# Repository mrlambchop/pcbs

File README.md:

pcbs
====

Various PCBs I fabbed at OSH Park

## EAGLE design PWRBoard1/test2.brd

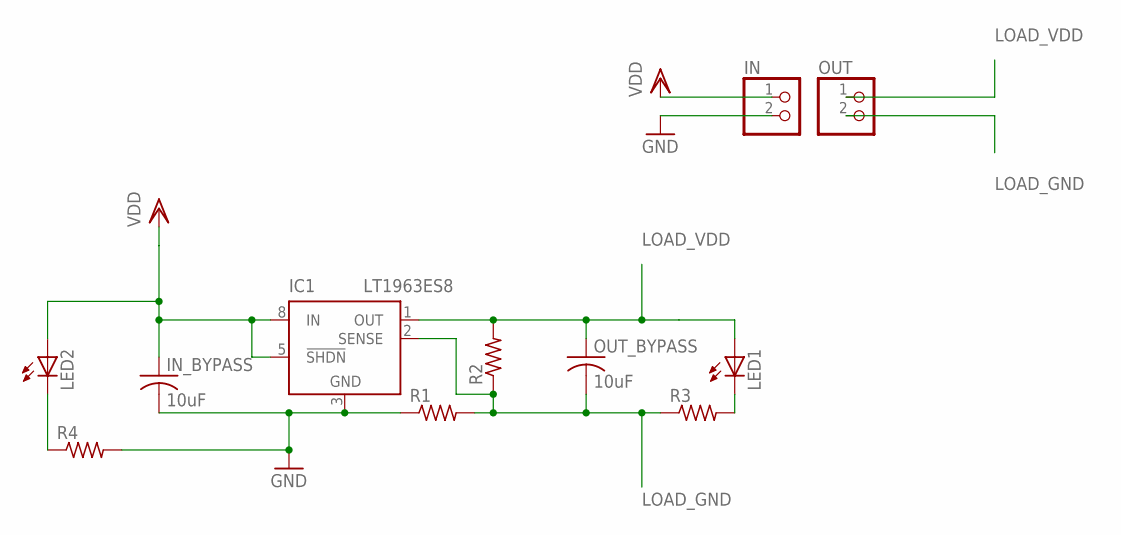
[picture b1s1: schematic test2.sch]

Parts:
IC1: LT1963ES8; SOIC8
IN: PINHD-1X2; 1X02
IN_BYPASS: 10uF; C1206
LED1, LED2: LEDCHIPLED_1206; CHIPLED_1206
OUT: PINHD-1X2; 1X02
OUT_BYPASS: 10uF; C1206
R1, R2, R3, R4: R-US_R1206; R1206

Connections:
GND: IC1.3 (GND), IC1.6 (GND), IC1.7 (GND), IN.2, IN_BYPASS.2, R1.1, R4.2
LOAD_GND: IC1.2 (SENSE), OUT.2, OUT_BYPASS.2, R1.2, R2.1, R3.1
LOAD_VDD: IC1.1 (OUT), LED1.A, OUT.1, OUT_BYPASS.1, R2.2
unnamed: LED2.C, R4.1
unnamed: LED1.C, R3.2
VDD: IC1.5 (!SHDN), IC1.8 (IN), IN.1, IN_BYPASS.1, LED2.A

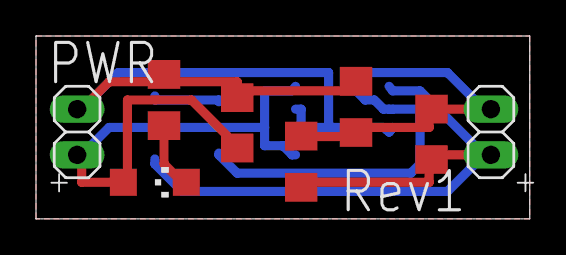
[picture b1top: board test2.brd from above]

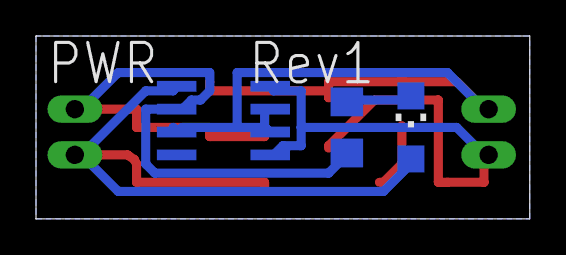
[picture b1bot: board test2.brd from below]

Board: 2 copper layers, 27.4 x 10.2 mm, 11 parts (3 on the bottom side), 6 nets.

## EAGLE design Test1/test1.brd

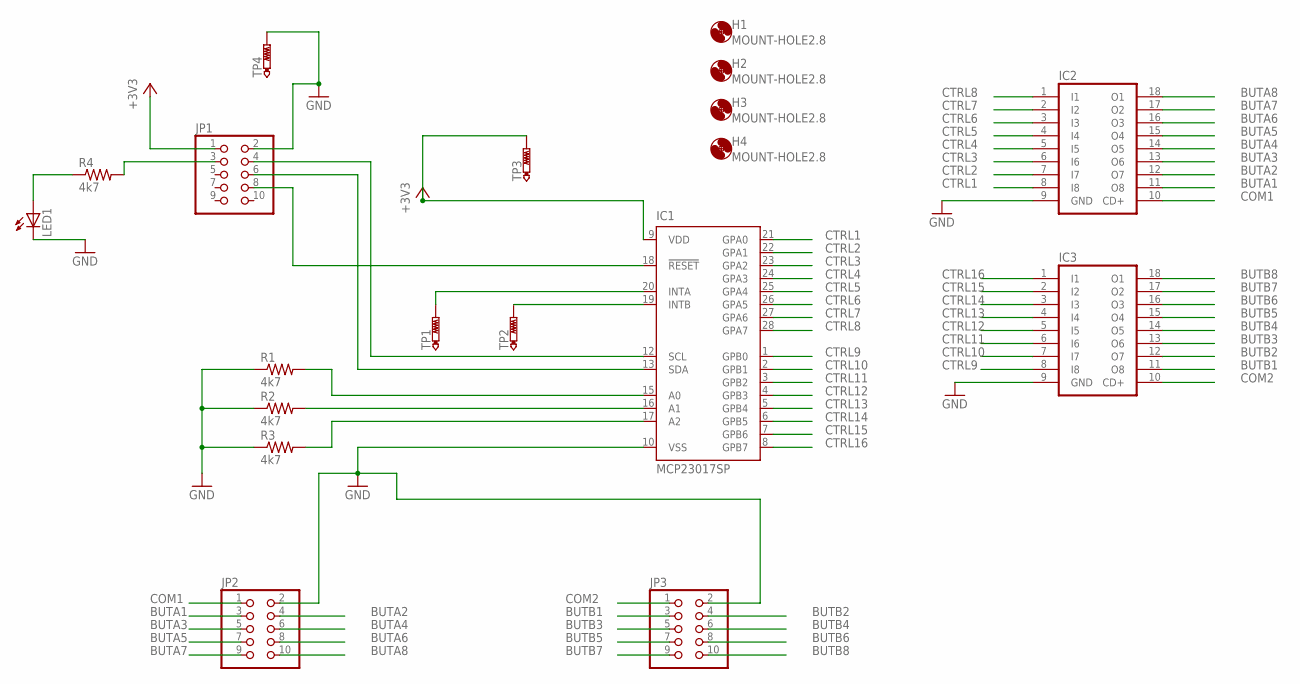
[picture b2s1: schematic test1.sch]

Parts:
H1, H2, H3, H4: MOUNT-HOLE2.8; 2,8
IC1: MCP23017SP; DIL28-3
IC2, IC3: ULN2803A; DIL18
JP1, JP2, JP3: PINHD-2X5; 2X05
LED1: LED5MM
R1, R2, R3, R4: 4k7; 0207/2V
TP1, TP2, TP3, TP4: PTR1B2,54; B2,54

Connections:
+3V3: IC1.9 (VDD), JP1.1, TP3.TP
BUTA1: IC2.11 (O8), JP2.3
BUTA2: IC2.12 (O7), JP2.4
BUTA3: IC2.13 (O6), JP2.5
BUTA4: IC2.14 (O5), JP2.6
BUTA5: IC2.15 (O4), JP2.7
BUTA6: IC2.16 (O3), JP2.8
BUTA7: IC2.17 (O2), JP2.9
BUTA8: IC2.18 (O1), JP2.10
BUTB1: IC3.11 (O8), JP3.3
BUTB2: IC3.12 (O7), JP3.4
BUTB3: IC3.13 (O6), JP3.5
BUTB4: IC3.14 (O5), JP3.6
BUTB5: IC3.15 (O4), JP3.7
BUTB6: IC3.16 (O3), JP3.8
BUTB7: IC3.17 (O2), JP3.9
BUTB8: IC3.18 (O1), JP3.10
COM1: IC2.10 (CD+), JP2.1
COM2: IC3.10 (CD+), JP3.1
CTRL1: IC1.21 (GPA0), IC2.8 (I8)
CTRL2: IC1.22 (GPA1), IC2.7 (I7)
CTRL3: IC1.23 (GPA2), IC2.6 (I6)
CTRL4: IC1.24 (GPA3), IC2.5 (I5)
CTRL5: IC1.25 (GPA4), IC2.4 (I4)
CTRL6: IC1.26 (GPA5), IC2.3 (I3)
CTRL7: IC1.27 (GPA6), IC2.2 (I2)
CTRL8: IC1.28 (GPA7), IC2.1 (I1)
CTRL9: IC1.1 (GPB0), IC3.8 (I8)
CTRL10: IC1.2 (GPB1), IC3.7 (I7)
CTRL11: IC1.3 (GPB2), IC3.6 (I6)
CTRL12: IC1.4 (GPB3), IC3.5 (I5)
CTRL13: IC1.5 (GPB4), IC3.4 (I4)
CTRL14: IC1.6 (GPB5), IC3.3 (I3)
CTRL15: IC1.7 (GPB6), IC3.2 (I2)
CTRL16: IC1.8 (GPB7), IC3.1 (I1)
GND: IC1.10 (VSS), IC2.9 (GND), IC3.9 (GND), JP1.2, JP2.2, JP3.2, LED1.K (C), R1.1, R2.1, R3.1, TP4.TP
unnamed: IC1.13 (SDA), JP1.6
unnamed: IC1.12 (SCL), JP1.4
unnamed: IC1.15 (A0), R1.2
unnamed: IC1.16 (A1), R2.2
unnamed: IC1.17 (A2), R3.2
unnamed: IC1.18 (!RESET), JP1.8
unnamed: JP1.3, R4.2
unnamed: LED1.A, R4.1
unnamed: IC1.20 (INTA), TP1.TP
unnamed: IC1.19 (INTB), TP2.TP

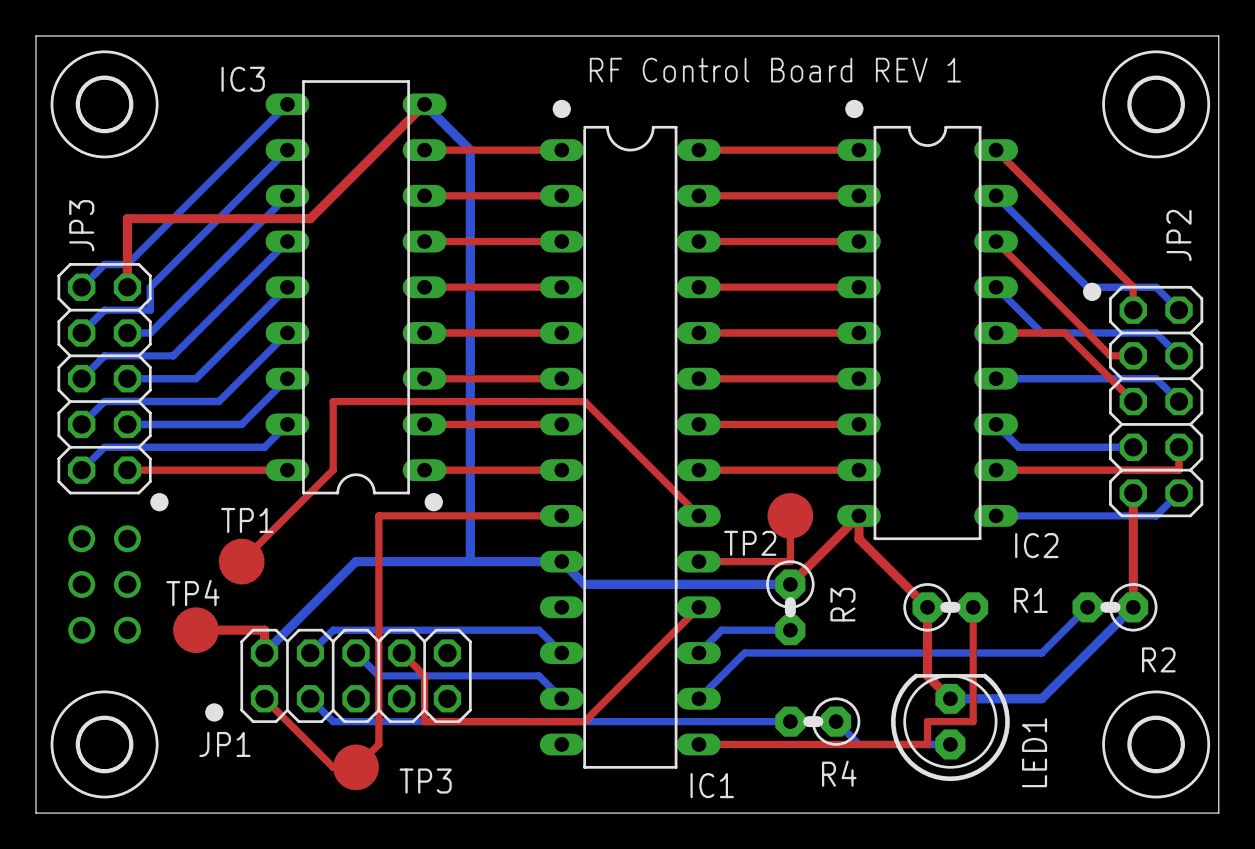
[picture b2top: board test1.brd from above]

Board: 2 copper layers, 65.7 x 43.2 mm, 19 parts (0 on the bottom side), 46 nets.

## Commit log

2014-01-03 Board file as submitted to OSH Park (Test1 - see how the fab service works)
2014-02-12 Add in the power board
